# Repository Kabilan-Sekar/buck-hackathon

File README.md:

# buck-hackathon
# Buck Converter Design Project

This repository contains the design files, simulation results, and PCB layout for a **Buck Converter** (step-down DC-DC power converter).

---

## Repository Structure

| Folder | Contents | Key Files Included |
| :--- | :--- | :--- |
| `design/` | Simulation models and control loop analysis. | `finalbuck.slk`, `bode_plot.png`, `waveforms.png` |
| `pcb/` | Printed Circuit Board (PCB) fabrication and assembly files. | `layout.kicad_pcb`, `schematic.kicad_sch`, `bom.xlsx` |
| (root) | General project documentation and high-level files. | `bonus_task.pdf`, `control_diagram.pdf` |

---

## Design and Analysis Files (`design/` folder)

* **`finalbuck.slk`**: The main **Simulink Model** used for the transient and steady-state simulation of the converter.
* **`bode_plot.png`**: Image showing the **Bode Plot** of the control loop, critical for verifying stability (phase and gain margins).
* **`waveforms.png`**: Image of key **time-domain waveforms** from the simulation (e.g., output voltage ripple, inductor current).
* **`notes.txt`**: General observations and design notes.

---

## PCB Files (`pcb/` folder)

The PCB was designed using **KiCad Board 9.0**.

* **`schematic.kicad_sch`**: The complete circuit diagram and component definitions.
* **`layout.kicad_pcb`**: The physical board layout and routing.
* **`bom.xlsx`**: The **Bill of Materials (BOM)** listing all required components for assembly.

---

## Documentation (Root directory)

* **`control_diagram.pdf`**: PDF detailing the **control strategy** and block diagram used for the feedback system.
* **`bonus_task.pdf`**: Document related to an extended design specification or analysis task.

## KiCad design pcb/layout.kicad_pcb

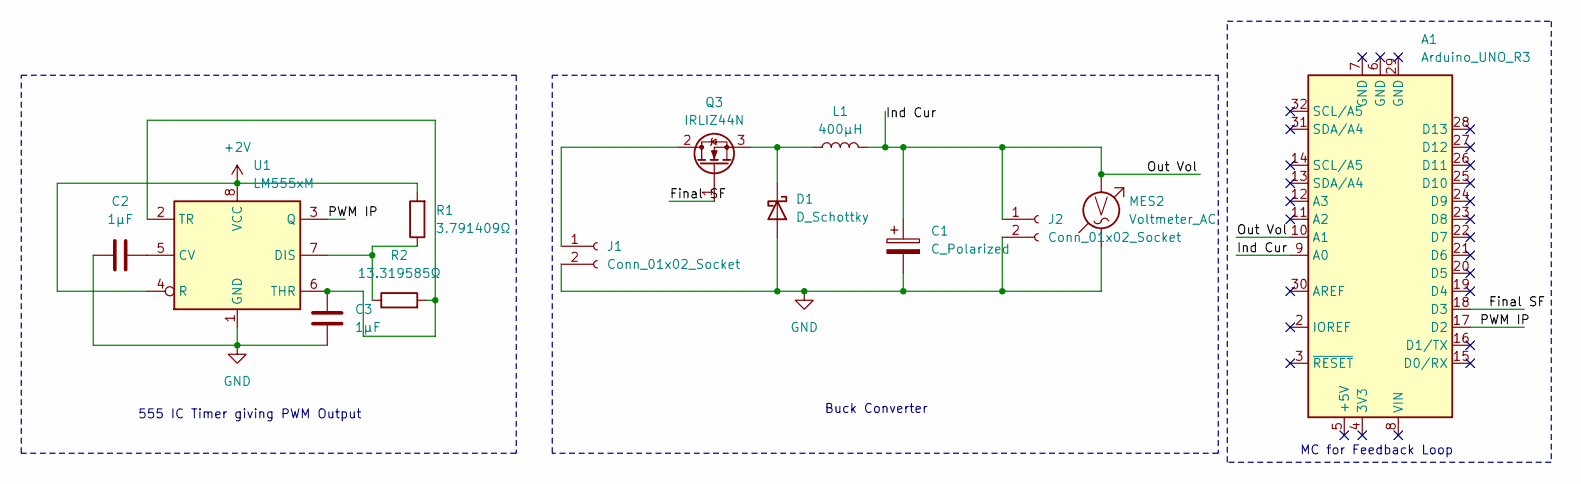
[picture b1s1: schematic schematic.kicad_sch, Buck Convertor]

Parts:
A1: Arduino_UNO_R3
C1: C_Polarized; CP_Axial_L10.0mm_D4.5mm_P15.00mm_Horizontal
C2, C3: 1μF; C_Axial_L3.8mm_D2.6mm_P12.50mm_Horizontal
D1: D_Schottky; D_DO-41_SOD81_P7.62mm_Horizontal
J1, J2: Conn_01x02_Socket; PinSocket_1x02_P2.54mm_Horizontal
L1: 400μH; L_Axial_L6.6mm_D2.7mm_P2.54mm_Vertical_Vishay_IM-2
MES2: Voltmeter_AC; TerminalBlock_4Ucon_1x02_P3.50mm_Horizontal
Q3: IRLIZ44N; TO-220F-3_Vertical
R1: 3.791409Ω; R_Axial_DIN0617_L17.0mm_D6.0mm_P20.32mm_Horizontal
R2: 13.319585Ω; R_Axial_DIN0309_L9.0mm_D3.2mm_P25.40mm_Horizontal
U1: LM555xM; SOIC-8_3.9x4.9mm_P1.27mm

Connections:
+2V: R1.2, U1.4 (R), U1.8 (VCC)
/Final SF: A1.18 (D3), Q3.1 (G)
/Ind Cur: A1.9 (A0), A1.10 (A1), C1.1, J2.1, L1.2, MES2.2
/PWM IP: A1.17 (D2), U1.3 (Q)
GND: C1.2, C2.1, C3.2, D1.2 (A), J1.2, J2.2, MES2.1, U1.1 (GND)
unnamed: D1.1 (K), L1.1, Q3.3 (S)
unnamed: J1.1, Q3.2 (D)
unnamed: C2.2, U1.5 (CV)
unnamed: R1.1, R2.1, U1.7 (DIS)
unnamed: C3.1, R2.2, U1.2 (TR), U1.6 (THR)

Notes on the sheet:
555 IC Timer giving PWM Output
MC for Feedback Loop
Buck Converter

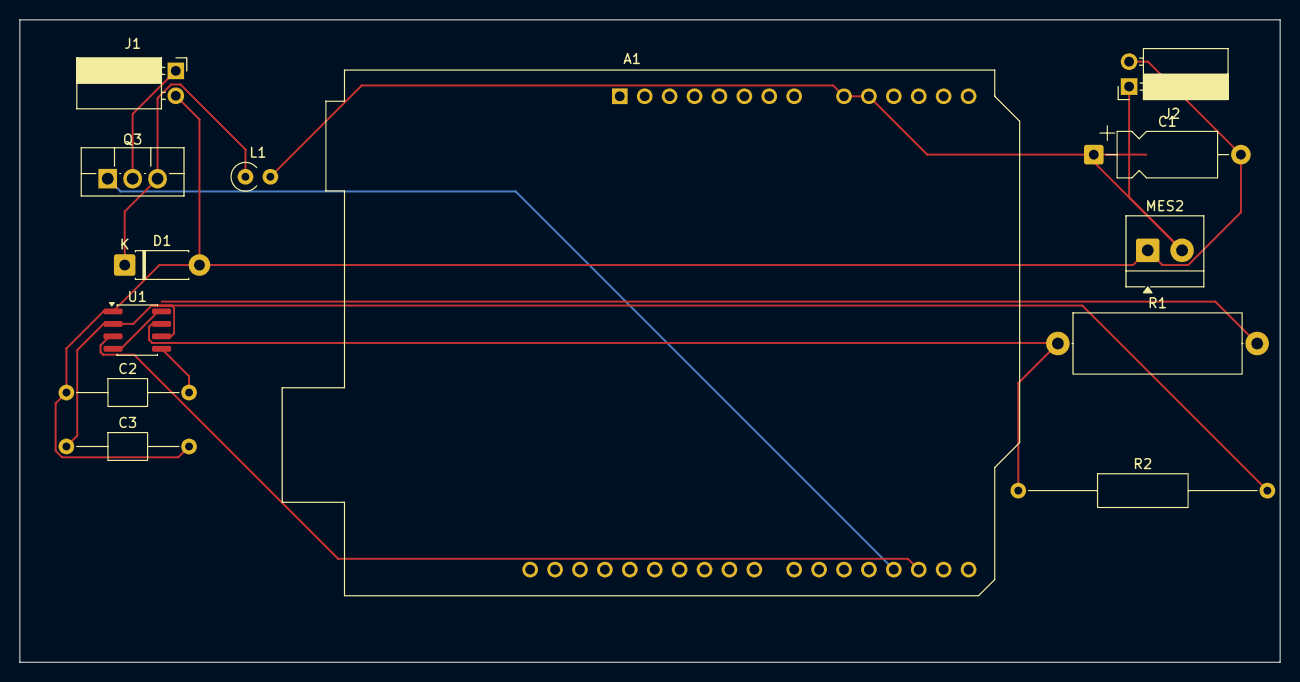
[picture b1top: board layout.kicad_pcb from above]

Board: 2 copper layers, 128.5 x 65.5 mm, 13 parts (0 on the bottom side), 10 nets.
